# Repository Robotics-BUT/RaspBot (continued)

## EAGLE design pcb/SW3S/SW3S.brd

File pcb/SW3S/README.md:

Modul odpojovace 3-clankove baterie
===================================

Modul ma za ukol ovladat balancer po sbernici a dle vysledku ovladat povoleni 
zapinani a vypinani robota tak aby nedoslo k poskozeni baterie. Sekundarni funkci
je jednoduchy rezim nabijeni baterie za pomoci klasickeho 12V AC/DC adapteru
(trafo do zdi) a hlavne ovladani ukonceni nabijeni v okamziku dosazeni max
napeti na clanek.

Modul ve vypnutem stavu nesmi odebirat velky klidovy proud, pocita se s trvalym
pripojenim na baterii. Po stisku tlacitka (sepnuti spinace) si obvod zmeri kondici
baterie a usoudi zdali je mozno pripojit zbytek robota. Po pripojeni napajeni se
periodicky dotazuje balancovacich jednotek na stav a v pripade poklesu napeti k
3.2V/clanek automaticky odpoji zatez.

Po pripojeni externiho adapteru tuto udalost musi byt modul schopen zdetekovat a
zahajit nabijeni, pokud baterie jeste nema plny stav nabiti. Behem nabijeni opet
kontrolovat kondici baterie a pri jakemkoliv problemu (teplota nabijeciho T,
teplota jakehokoliv balancovaciho T, napeti na clanku) nabijeni odpojit. Pri
podbiti baterie pod 3V/clanek zakazat nabijeni.

Modul ma tez jistici funkci, proti zkratu na vystupu, zkratu na nabijeci
sbernici musi prehoret pojistka (prozatim rychla 2A) a nesmi se poskodit ani
elektronika ani baterie.

Pozadavky:
----------
Klidovy proud (OFF) = max 220 uA avg (vybije 2200mAh baterii za 1 rok)
Aktivni proud (ON) = max 10mA avg (dotazuje se na stav clanku)
Mereni teploty regulacniho tranzistoru, zakaz nabijeni nad danou mez)
Obousmerna komunikace s BAL3S
Nizka cena (vzhledem k cene baterie - tj pod 400kc/kus)
Velikost tak aby se modul dal prilepit na baterii a byl s ni trvale spojeny.

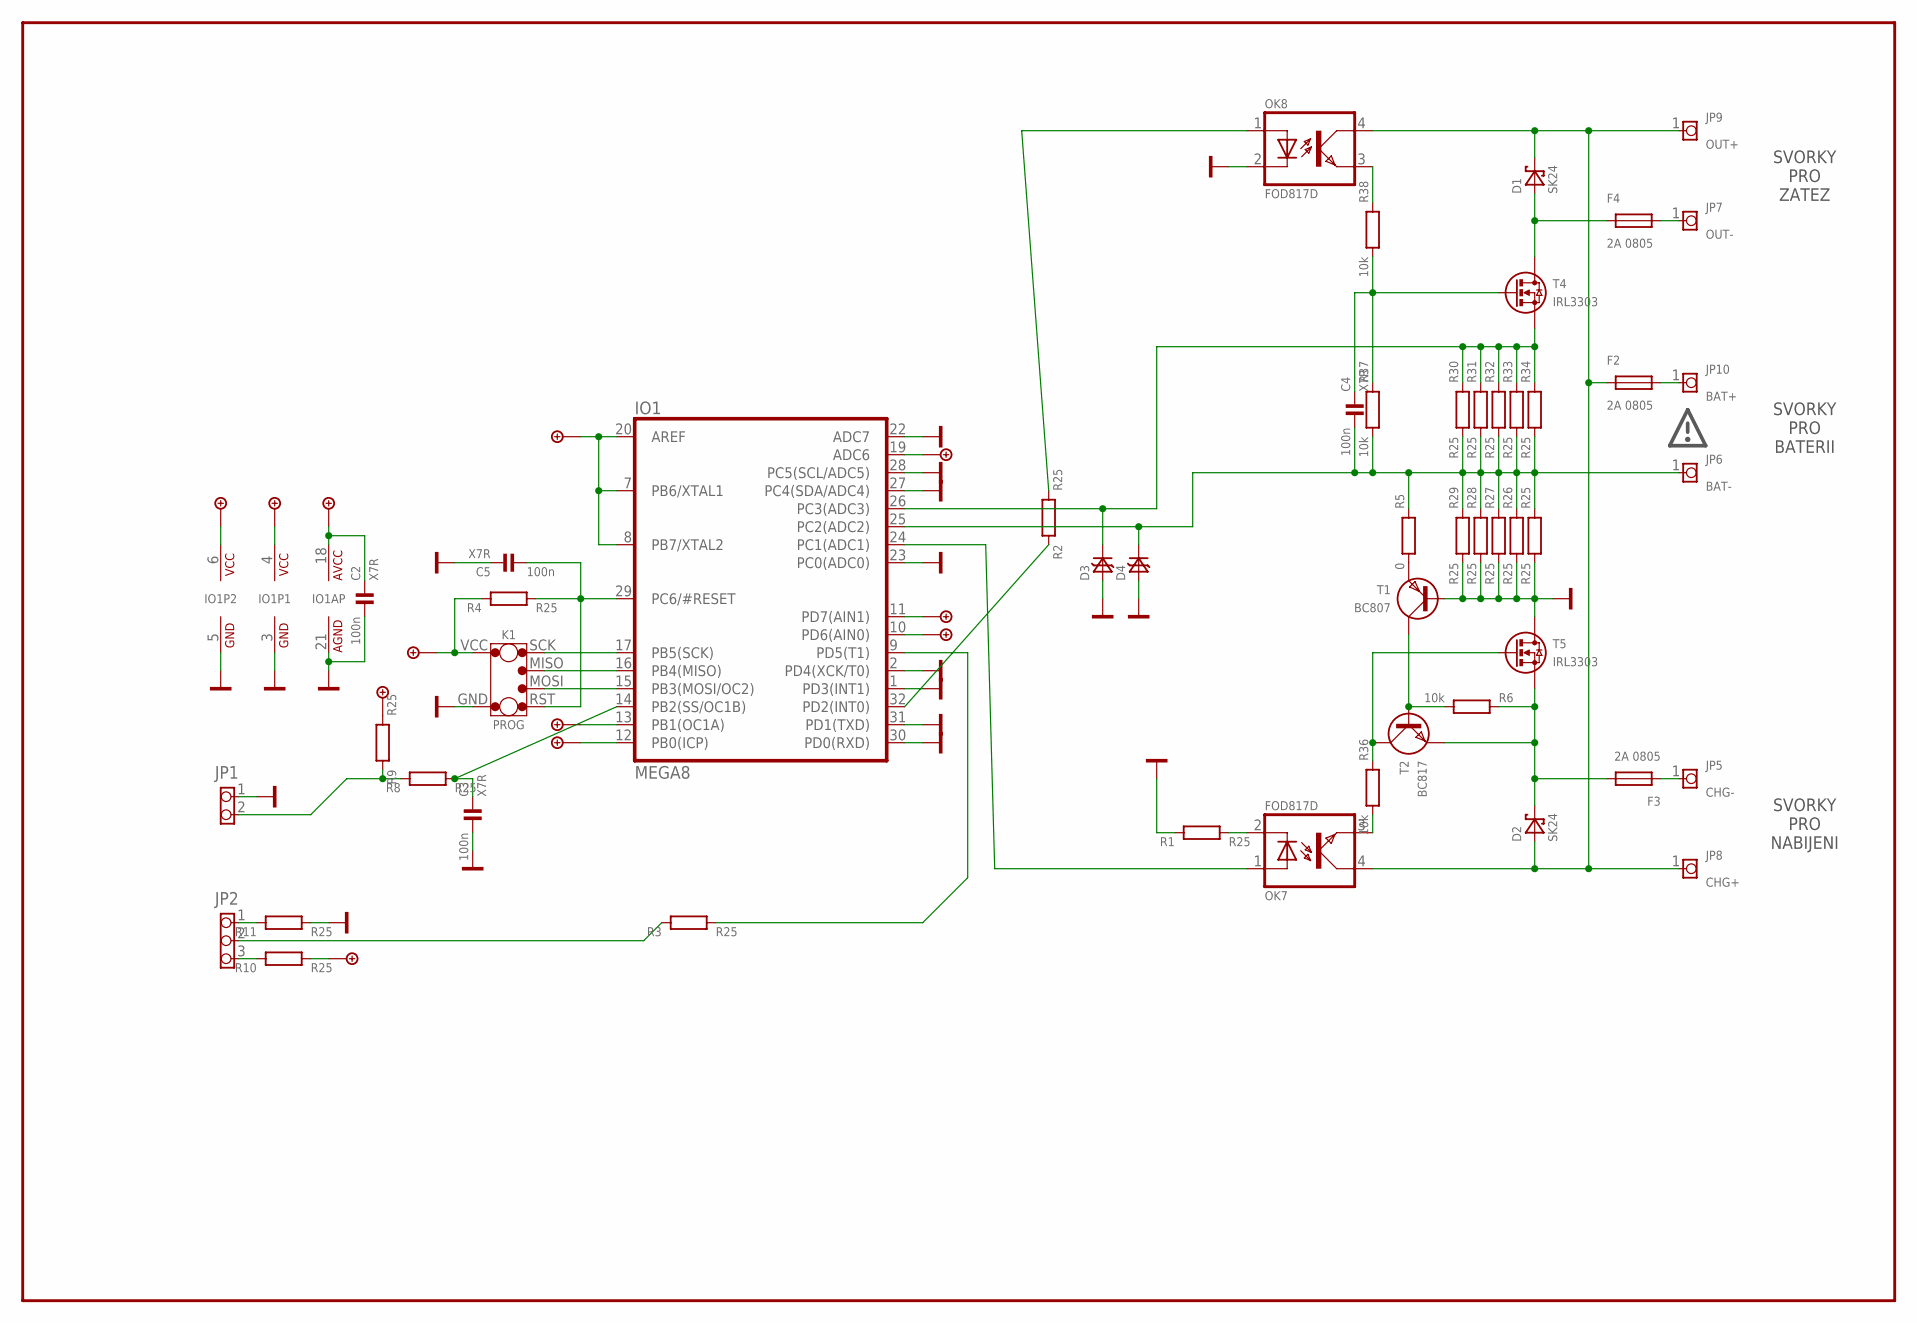
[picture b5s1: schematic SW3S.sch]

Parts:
C2, C3, C4, C5: 100n; 0805
D1, D2: SK24; D_SMB
D3, D4: D_TRANSIL_MLL34; D_MLL34
F2, F3, F4: 2A 0805; 0805
IO1: MEGA8; TQFP32
JP1: PINHD-1X2_254_EDGE; 1X02_254_EDGE
JP2: PINHD-1X3_254_EDGE; 1X03_254_EDGE
JP5: CHG-; 1X01_254_PAD
JP6: BAT-; 1X01_254_PAD
JP7: OUT-; 1X01_254_PAD
JP8: CHG+; 1X01_254_PAD
JP9: OUT+; 1X01_254_PAD
JP10: BAT+; 1X01_254_PAD
K1: PROG
OK7, OK8: FOD817D; SO04
R1, R2, R3, R4, R8, R9, R10, R11, R25, R26, R27, R28, R29, R30, R31, R32, R33, R34: R25; 0805
R5: 0; 0805
R6, R36, R37, R38: 10k; 0805
T1: BC807; SOT23
T2: BC817; SOT23
T4, T5: IRL3303; TO252

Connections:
+5V: C2.1, IO1.4 (VCC), IO1.6 (VCC), IO1.7 (PB6/XTAL1), IO1.8 (PB7/XTAL2), IO1.10 (PD6(AIN0)), IO1.11 (PD7(AIN1)), IO1.12 (PB0(ICP)), IO1.13 (PB1(OC1A)), IO1.18 (VCC), IO1.19 (ADC6), IO1.20 (AREF), K1.VCC, R4.2, R9.1, R10.1
BAT+: F2.2, JP10.1
BAT-: C4.2, D4.K, IO1.25 (PC2(ADC2)), JP6.1, R5.2, R25.2, R26.2, R27.2, R28.2, R29.2, R30.1, R31.1, R32.1, R33.1, R34.1, R37.1
CHG-: F3.1, JP5.1
GND: C2.2, C3.2, C5.1, D3.A, D4.A, IO1.1 (PD3(INT1)), IO1.2 (PD4(XCK/T0)), IO1.3 (GND), IO1.5 (GND), IO1.21 (GND), IO1.22 (ADC7), IO1.23 (PC0(ADC0)), IO1.27 (PC4(SDA/ADC4)), IO1.28 (PC5(SCL/ADC5)), IO1.30 (PD0(RXD)), IO1.31 (PD1(TXD)), JP1.1, K1.GND, OK8.2 (C), R1.2, R11.1, R25.1, R26.1, R27.1, R28.1, R29.1, T1.1 (B), T5.2 (D)
unnamed: IO1.17 (PB5(SCK)), K1.SCK
unnamed: IO1.16 (PB4(MISO)), K1.MISO
unnamed: IO1.15 (PB3(MOSI/OC2)), K1.MOSI
unnamed: C5.2, IO1.29 (PC6/#RESET), K1.RST, R4.1
unnamed: IO1.32 (PD2(INT0)), R2.2
unnamed: IO1.9 (PD5(T1)), R3.1
unnamed: R6.1, T1.2 (C), T2.1 (B)
unnamed: R36.2, T2.2 (C), T5.1 (G)
unnamed: OK7.3 (EMIT), R36.1
unnamed: IO1.24 (PC1(ADC1)), OK7.1 (A)
unnamed: D2.K, F3.2, R6.2, T2.3 (E), T5.3 (S)
unnamed: F4.2, JP7.1
unnamed: OK7.2 (C), R1.1
unnamed: C3.1, IO1.14 (PB2(SS/OC1B)), R8.1
unnamed: JP1.2, R8.2, R9.2
unnamed: JP2.2, R3.2
unnamed: JP2.3, R10.2
unnamed: JP2.1, R11.2
unnamed: R5.1, T1.3 (E)
unnamed: OK8.1 (A), R2.1
unnamed: D3.K, IO1.26 (PC3(ADC3)), R30.2, R31.2, R32.2, R33.2, R34.2, T4.3 (S)
unnamed: OK8.3 (EMIT), R38.2
unnamed: C4.1, R37.2, R38.1, T4.1 (G)
OUT+: D1.K, D2.A, F2.1, JP8.1, JP9.1, OK7.4 (COL), OK8.4 (COL)
OUT-: D1.A, F4.1, T4.2 (D)

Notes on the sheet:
SVORKY PRO ZATEZ
SVORKY PRO BATERII
SVORKY PRO NABIJENI

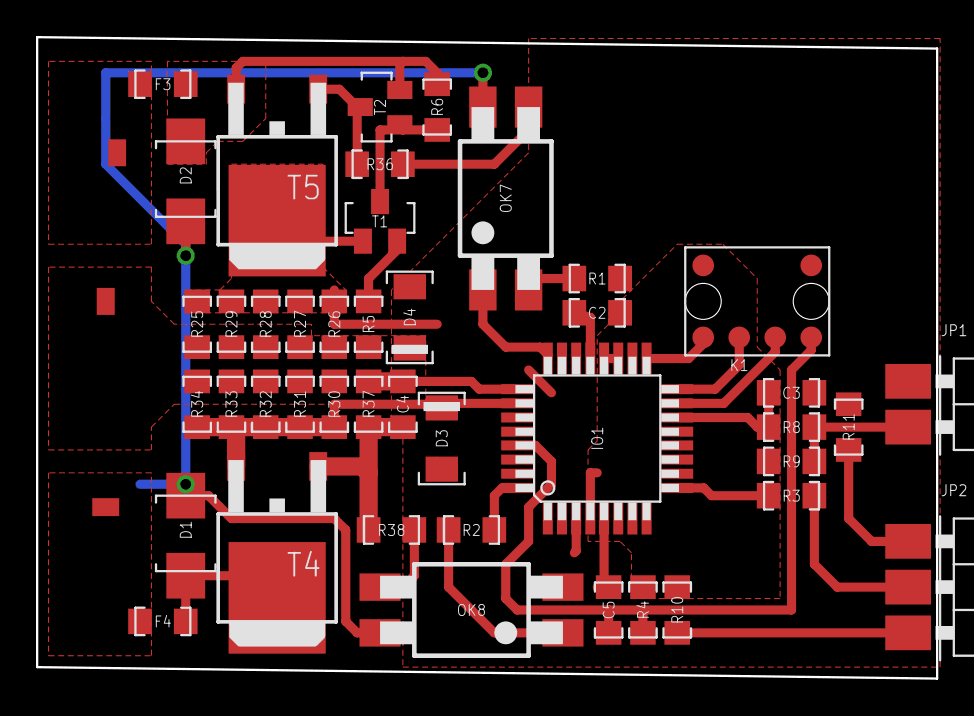
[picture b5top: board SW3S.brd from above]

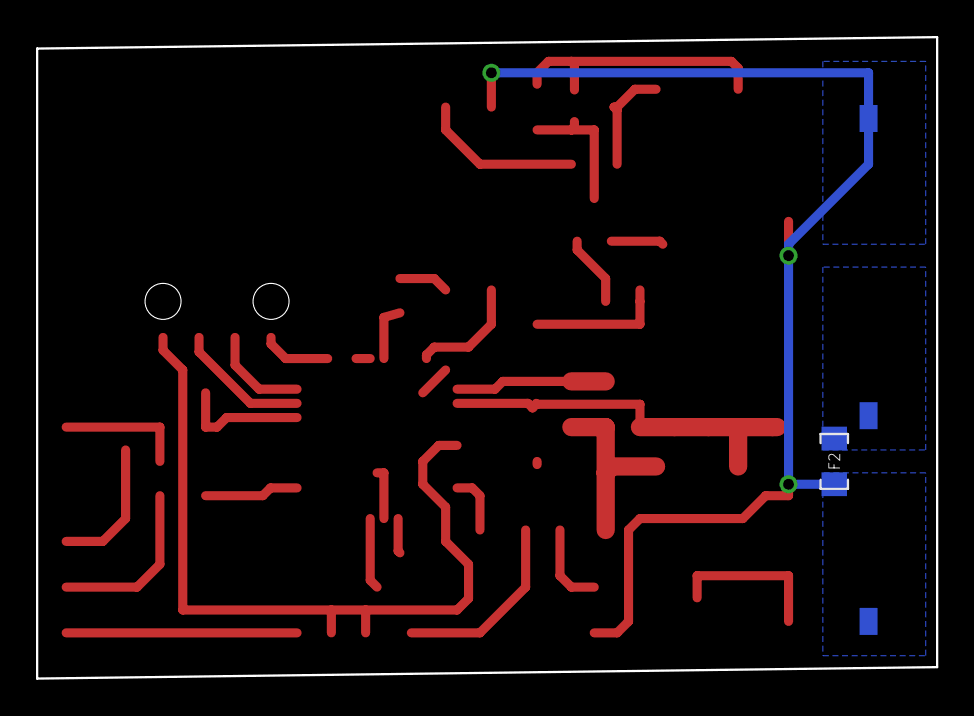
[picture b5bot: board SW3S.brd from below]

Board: 2 copper layers, 50.0 x 35.6 mm, 50 parts (4 on the bottom side), 30 nets.

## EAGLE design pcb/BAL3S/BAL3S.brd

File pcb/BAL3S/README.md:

Modul balanceru 3-clankove baterie
==================================

Modul ma za ukol merit napeti na jednotlivych clancich baterie a nasledne
stavove informace posilat ven pomoci sbernice. Pokud neni pripojen master
na sbernici, je nutne odpojit balancovani a mit nizkou spotrebu vzhledem ke
kapacite baterie.

Pozadavky:
----------
Klidovy proud = max 220 uA avg (vybije 2200mAh baterii za 1 rok)
Balancovaci proud = cca 100 mA DC / clanek (0.5W/clanek je treba uchladit)
Aktivni proud = max 2mA avg (master se dotazuje na stav clanku)
Mereni napeti kazdeho clanku 4.200V s rozlisenim +- 5mV (10 bit ADC}
Mereni teploty topneho tranzistoru, zakaz balancovani nad danou mez)
Obousmerna komunikace s vyvazovacim procesorem kazdeho clanku
Moznost kalibrace mereneho napeti pres sbernici (vicebod ?)
Nizka cena (vzhledem k cene baterie - tj pod 400kc/kus)
Velikost tak aby se modul dal prilepit na baterii a byl s ni trvale spojeny.

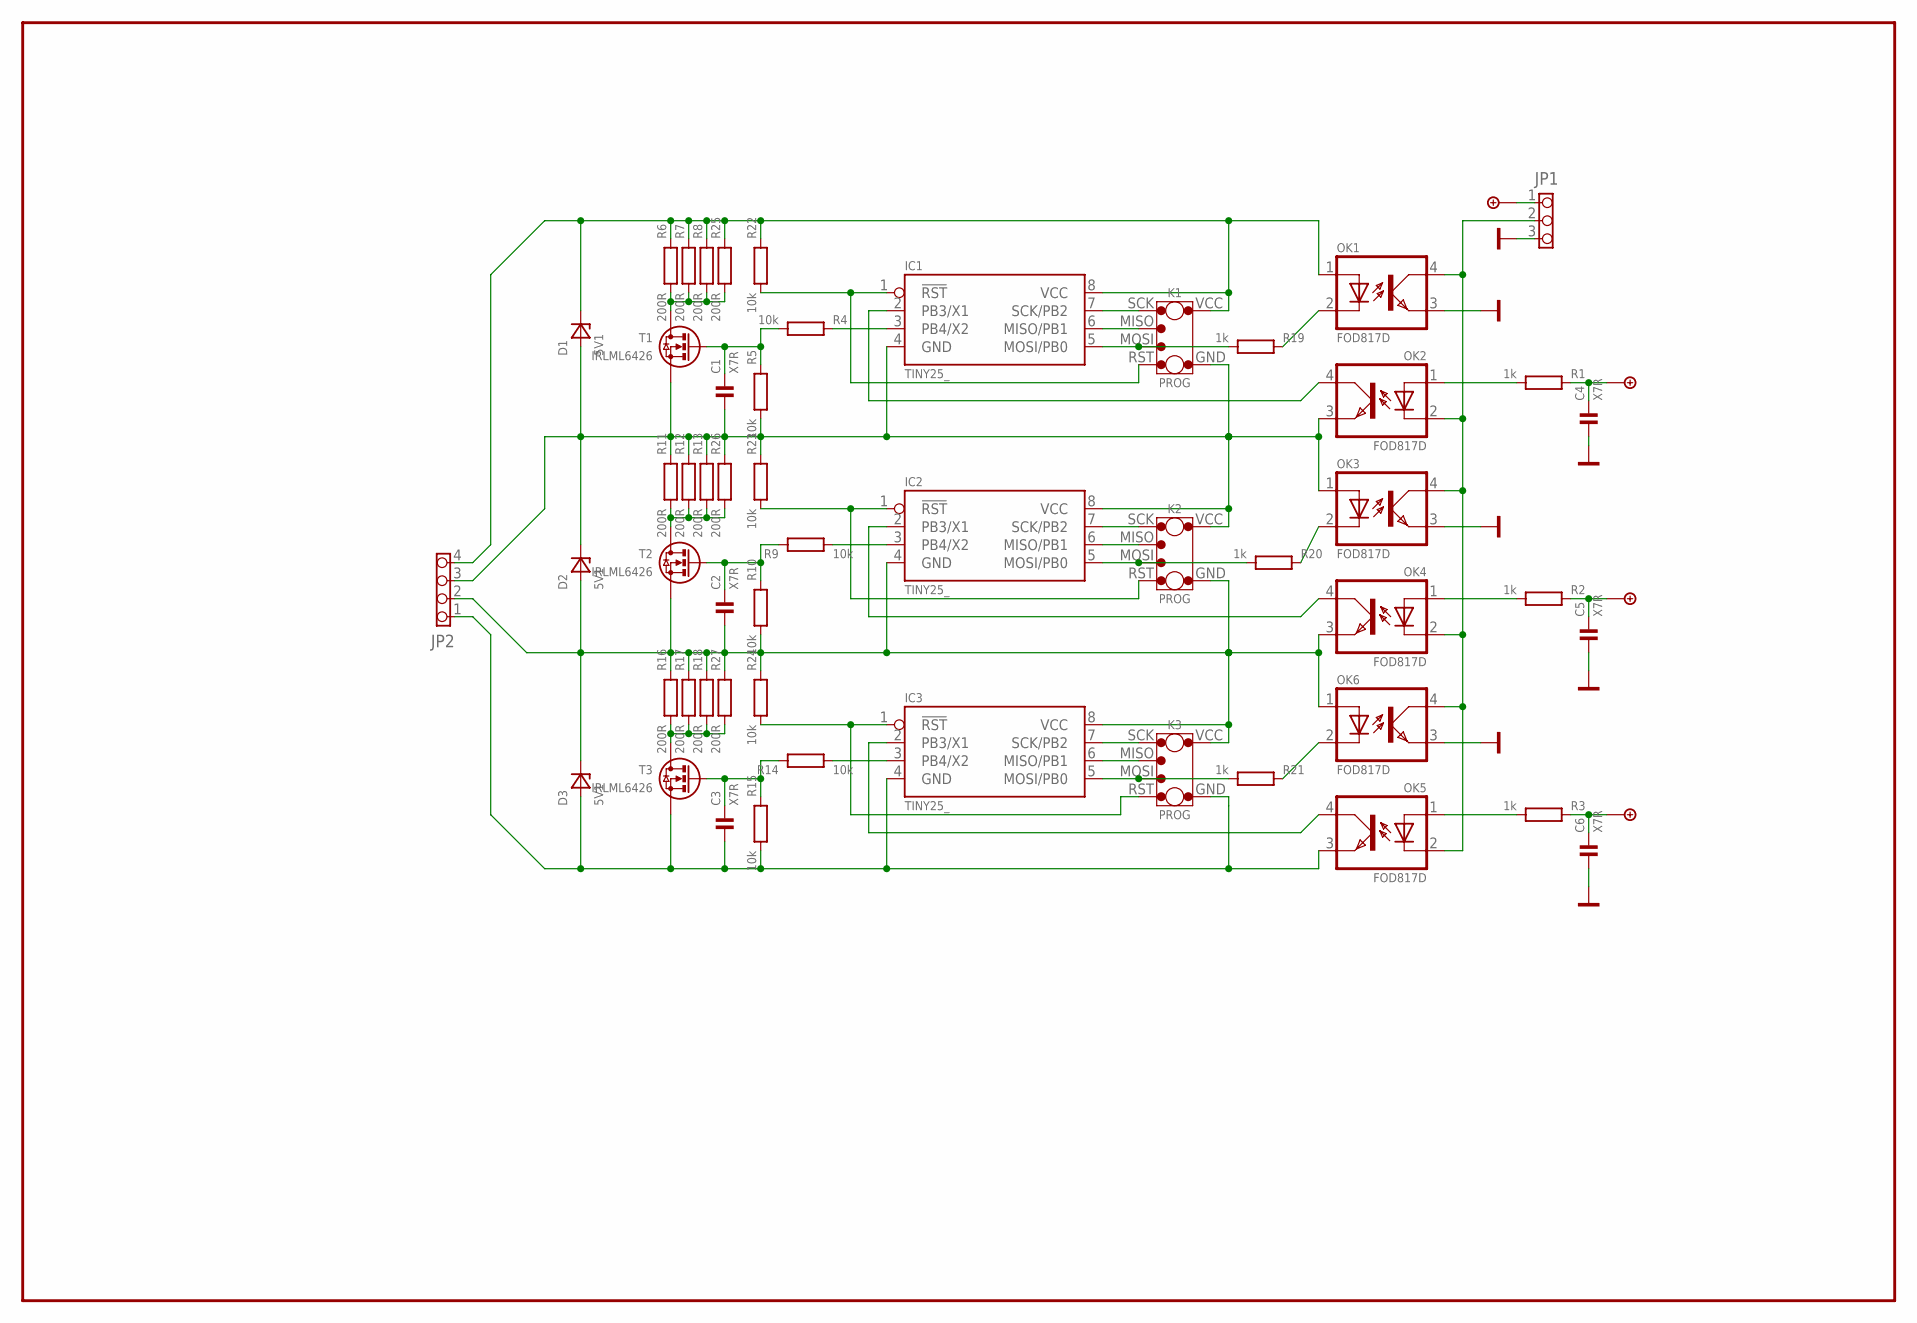
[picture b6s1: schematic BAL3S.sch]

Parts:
C1, C2, C3, C4, C5, C6: C0805; 0805
D1, D2, D3: 5V1; D_MLL41
IC1, IC2, IC3: TINY25_; SO08
JP1: PINHD-1X3_254_EDGE; 1X03_254_EDGE
JP2: PINHD-1X4_254_EDGE; 1X04_254_EDGE
K1, K2, K3: PROG
OK1, OK2, OK3, OK4, OK5, OK6: FOD817D; SO04
R1, R2, R3, R19, R20, R21: 1k; 0805
R4, R5, R9, R10, R14, R15, R22, R23, R24: 10k; 0805
R6, R7, R8, R11, R12, R13, R16, R17, R18, R25, R26, R27: 200R; 0805
T1, T2, T3: IRLML6426; SOT23

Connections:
+5V: C4.1, C5.1, C6.1, JP1.1, R1.2, R2.2, R3.2
GND: C4.2, C5.2, C6.2, JP1.3, OK1.3 (EMIT), OK3.3 (EMIT), OK6.3 (EMIT)
unnamed: C1.2, D1.A, D2.K, IC1.4 (GND), IC2.8 (VCC), JP2.3, K1.GND, K2.VCC, OK2.3 (EMIT), OK3.1 (A), R5.1, R11.2, R12.2, R13.2, R23.2, R26.2, T1.3 (S)
unnamed: C2.2, D2.A, D3.K, IC2.4 (GND), IC3.8 (VCC), JP2.2, K2.GND, K3.VCC, OK4.3 (EMIT), OK6.1 (A), R10.1, R16.2, R17.2, R18.2, R24.2, R27.2, T2.3 (S)
unnamed: C3.2, D3.A, IC3.4 (GND), JP2.1, K3.GND, OK5.3 (EMIT), R15.1, T3.3 (S)
unnamed: IC1.3 (PB4/X2), R4.2
unnamed: JP1.2, OK1.4 (COL), OK2.2 (C), OK3.4 (COL), OK4.2 (C), OK5.2 (C), OK6.4 (COL)
unnamed: OK2.1 (A), R1.1
unnamed: OK4.1 (A), R2.1
unnamed: OK5.1 (A), R3.1
unnamed: C1.1, R4.1, R5.2, T1.1 (G)
unnamed: IC1.2 (PB3/X1), OK2.4 (COL)
unnamed: IC1.7 (SCK/PB2), K1.SCK
unnamed: R6.1, R7.1, R8.1, R25.1, T1.2 (D)
unnamed: C2.1, R9.2, R10.2, T2.1 (G)
unnamed: D1.K, IC1.8 (VCC), JP2.4, K1.VCC, OK1.1 (A), R6.2, R7.2, R8.2, R22.2, R25.2
unnamed: IC2.3 (PB4/X2), R9.1
unnamed: IC2.2 (PB3/X1), OK4.4 (COL)
unnamed: R11.1, R12.1, R13.1, R26.1, T2.2 (D)
unnamed: IC1.6 (MISO/PB1), K1.MISO
unnamed: IC3.3 (PB4/X2), R14.1
unnamed: C3.1, R14.2, R15.2, T3.1 (G)
unnamed: R16.1, R17.1, R18.1, R27.1, T3.2 (D)
unnamed: IC1.5 (MOSI/PB0), K1.MOSI, R19.1
unnamed: IC1.1 (!RST), K1.RST, R22.1
unnamed: IC2.7 (SCK/PB2), K2.SCK
unnamed: IC2.6 (MISO/PB1), K2.MISO
unnamed: IC2.5 (MOSI/PB0), K2.MOSI, R20.1
unnamed: IC3.7 (SCK/PB2), K3.SCK
unnamed: IC2.1 (!RST), K2.RST, R23.1
unnamed: IC3.6 (MISO/PB1), K3.MISO
unnamed: IC3.5 (MOSI/PB0), K3.MOSI, R21.1
unnamed: IC3.1 (!RST), K3.RST, R24.1
unnamed: IC3.2 (PB3/X1), OK5.4 (COL)
unnamed: OK1.2 (C), R19.2
unnamed: OK3.2 (C), R20.2
unnamed: OK6.2 (C), R21.2

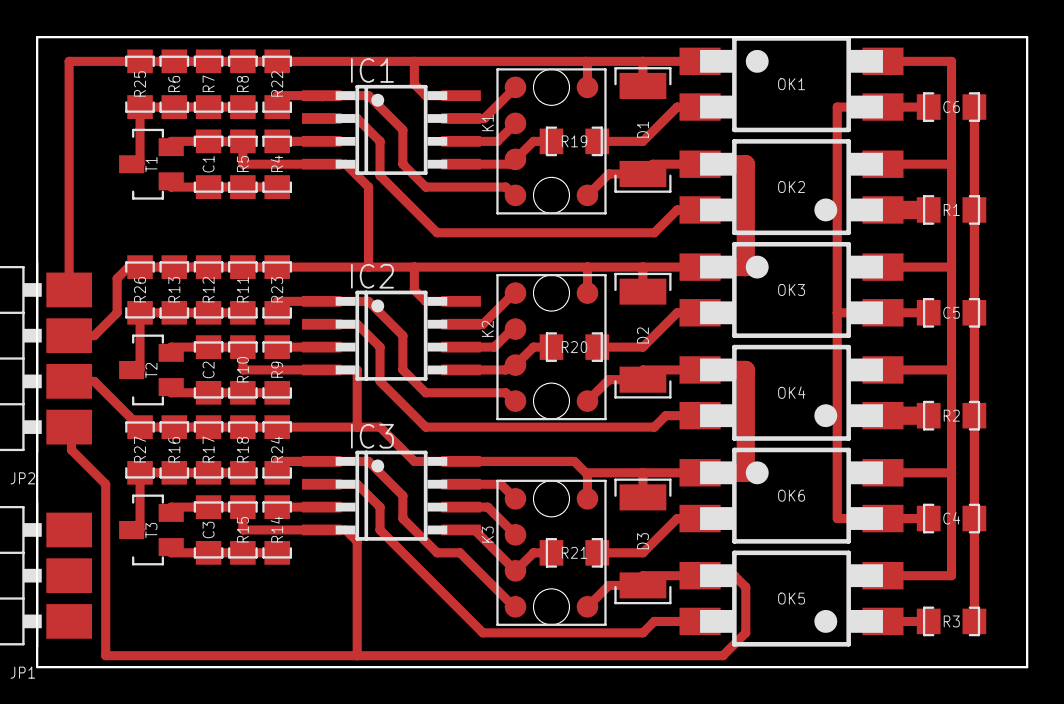
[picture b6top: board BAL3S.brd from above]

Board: 2 copper layers, 55.0 x 35.0 mm, 53 parts (0 on the bottom side), 37 nets.

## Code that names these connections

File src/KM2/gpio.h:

#ifndef GPIO_H__
#define GPIO_H__

#include <stdbool.h>
#include <avr/io.h>

/*
 * KM2/gpio.h:
 *	gpio low level module
 *
 * Copyright (c) 2016 Frantisek Burian <BuFran@seznam.cz>
 ***********************************************************************
 * This file is part of KAMBot
 *
 *    KAMBot is free software: you can redistribute it and/or modify
 *    it under the terms of the GNU Lesser General Public License as published by
 *    the Free Software Foundation, either version 3 of the License, or
 *    (at your option) any later version.
 *
 *    KAMBot is distributed in the hope that it will be useful,
 *    but WITHOUT ANY WARRANTY; without even the implied warranty of
 *    MERCHANTABILITY or FITNESS FOR A PARTICULAR PURPOSE.  See the
 *    GNU Lesser General Public License for more details.
 *
 *    You should have received a copy of the GNU Lesser General Public License
 *    along with KAMBot.  If not, see <http://www.gnu.org/licenses/>.
 ***********************************************************************
 */

#define _PA		(0 << 4)
#define _PA0	(_PA + 0)
#define _PA1	(_PA + 1)
#define _PA2	(_PA + 2)
#define _PA3	(_PA + 3)
#define _PA4	(_PA + 4)
#define _PA5	(_PA + 5)
#define _PA6	(_PA + 6)
#define _PA7	(_PA + 7)

#define _PB		(1 << 4)
#define _PB0	(_PB + 0)
#define _PB1	(_PB + 1)
#define _PB2	(_PB + 2)
#define _PB3	(_PB + 3)
#define _PB4	(_PB + 4)
#define _PB5	(_PB + 5)
#define _PB6	(_PB + 6)
#define _PB7	(_PB + 7)

#define _PC		(2 << 4)
#define _PC0	(_PC + 0)
#define _PC1	(_PC + 1)
#define _PC2	(_PC + 2)
#define _PC3	(_PC + 3)
#define _PC4	(_PC + 4)
#define _PC5	(_PC + 5)
#define _PC6	(_PC + 6)
#define _PC7	(_PC + 7)

#define _PD		(3 << 4)
#define _PD0	(_PD + 0)
#define _PD1	(_PD + 1)
#define _PD2	(_PD + 2)
#define _PD3	(_PD + 3)
#define _PD4	(_PD + 4)
#define _PD5	(_PD + 5)
#define _PD6	(_PD + 6)
#define _PD7	(_PD + 7)

#define _PE		(4 << 4)
#define _PE0	(_PE + 0)
#define _PE1	(_PE + 1)
#define _PE2	(_PE + 2)
#define _PE3	(_PE + 3)
#define _PE4	(_PE + 4)
#define _PE5	(_PE + 5)
#define _PE6	(_PE + 6)
#define _PE7	(_PE + 7)

#define _PF		(5 << 4)
#define _PF0	(_PF + 0)
#define _PF1	(_PF + 1)
#define _PF2	(_PF + 2)
#define _PF3	(_PF + 3)
#define _PF4	(_PF + 4)
#define _PF5	(_PF + 5)
#define _PF6	(_PF + 6)
#define _PF7	(_PF + 7)

#define __PORT(pin)		(pin & 0xF0)
#define __PIN(pin)		(pin & 0x0F)
#define __PINBIT(pin)	(1 << (pin & 0x0F))

inline void gpio_out(const char pin)
{
	switch (__PORT(pin)) {
//		case _PA: DDRA &= ~__PINBIT(pin); break;
		case _PB: DDRB &= ~__PINBIT(pin); break;
		case _PC: DDRC &= ~__PINBIT(pin); break;
		case _PD: DDRD &= ~__PINBIT(pin); break;
	}
}

inline void gpio_in(const char pin)
{
	switch (__PORT(pin)) {
//		case _PA: DDRA |= __PINBIT(pin); break;
		case _PB: DDRB |= __PINBIT(pin); break;
		case _PC: DDRC |= __PINBIT(pin); break;
		case _PD: DDRD |= __PINBIT(pin); break;
	}
}

inline void gpio_high(const char pin)
{
	switch (__PORT(pin)) {
//		case _PA: PORTA |= __PINBIT(pin); break;
		case _PB: PORTB |= __PINBIT(pin); break;
		case _PC: PORTC |= __PINBIT(pin); break;
		case _PD: PORTD |= __PINBIT(pin); break;
	}
}

inline void gpio_low(const char pin)
{
	switch (__PORT(pin)) {
	//	case _PA: PORTA &= ~__PINBIT(pin); break;
		case _PB: PORTB &= ~__PINBIT(pin); break;
		case _PC: PORTC &= ~__PINBIT(pin); break;
		case _PD: PORTD &= ~__PINBIT(pin); break;
	}
}

inline void gpio_toggle(const char pin)
{
	switch (__PORT(pin)) {
	//	case _PA: PORTA ^= __PINBIT(pin); break;
		case _PB: PORTB ^= __PINBIT(pin); break;
		case _PC: PORTC ^= __PINBIT(pin); break;
		case _PD: PORTD ^= __PINBIT(pin); break;
	}
}

inline void gpio_set(const char pin, const char value)
{
	switch (__PORT(pin)) {
#ifdef PORTA
		case _PA:
			if (value) PORTA |= __PINBIT(pin);
			else PORTA &= ~__PINBIT(pin);
			break;
#endif
#ifdef PORTB
		case _PB:
			if (value) PORTB |= __PINBIT(pin);
			else PORTB &= ~__PINBIT(pin);
			break;
#endif
#ifdef PORTC
		case _PC:
			if (value) PORTC |= __PINBIT(pin);
			else PORTC &= ~__PINBIT(pin);
			break;
#endif
#ifdef PORTD
		case _PD:
			if (value) PORTD |= __PINBIT(pin);
			else PORTD &= ~__PINBIT(pin);
			break;
#endif
	}
}

inline bool gpio_get(const char pin)
{
	switch (__PORT(pin)) {
	//	case _PA: return (PINA & __PINBIT(pin)) != 0;
		case _PB: return (PINB & __PINBIT(pin)) != 0;
		case _PC: return (PINC & __PINBIT(pin)) != 0;
		case _PD: return (PIND & __PINBIT(pin)) != 0;
	}
}


#endif //GPIO_H

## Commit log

2015-09-23 Added primary base tests of the platform
2015-09-23 Added readme
2015-09-23 Changed build system
2015-09-27 Added header library with pin definitions
2015-10-01 Pridan testovaci firmware pro cteni MCP3424 !! nutne opravy v knihovne wiringPi
2015-10-01 Added bigstepping - now very fast rotation
2015-10-02 Dual motor control
2015-10-02 Modified and fully working with joystick and dual motors
2015-10-02 Added UDP interface to Raspbot
2016-03-08 Pridana prvni verze plosnych spoju pro APU * jednotka BAL3S pro 3clankovy balancer * SW3S pro autimaticky odpojovac a nabijec
    momentalne je verze kdy lze nabijeci proud ridit (bude odstraneno)
2016-03-08 Pridany temporary soubory Eagle jako ignorovane
2016-03-08 Regulace maximalniho nabijeciho proudu neni potreba
    V prvni fazi se nabiji baterie konstantnim proudem a v pripade dosazeni U 4.15V/clanek (rezerva 50mV) se nabijeni uplne odpoji.
    V pripade kdy balancer nebude stihat vyvazit baterii se tez nabijeni odpoji do okamziku vyvazeni vsech clanku baterie pod mez danou fw.
    V pripade podvybiti baterie pod 3V elektronika nepovoli nabijeni (baterii je nutno nabit externi "inteligentni" nabijeckou.
    Pozor:
    Je potreba nabijet ze zdroje 12-14V kvuli ubytku napeti / ztratovem vykonu na regulacnim tranzistoru.
    Ve firmware musi byt odpojeni nabijeni v pripade prehrati CPU nad stanovenou, docela nizkou mez !!! (CPU je blizko regulacniho T)
2016-03-08 Prvni verze ovladace dvou krokovych motoru KM2
    Tato verze vychazi z hw 0.2, je potreba velky redesign pro snizeni montazni vysky. Vyuziti 2v DPS a drivery se budou pajet rovnou, bez patic.
    Je potreba tez specifikovat velikost DPS (probrat s navrharem mechanicke konstrukce)
2016-03-08 Vytvoreny slozky pro firmware modulu BAL3S, SW3S a KM2
2016-03-08 Pridany popisne soubory popisujici funkci jednotilvych modulu
2016-03-08 Zmena nazvu robota
2016-03-08 Pridany dalsi slozky stromove struktury projektu
2016-03-09 blikani s vypisem
2016-03-10 Pridana dokumentace modulu RPIV00 a error list.
2016-03-10 STL soubory pro uplne prvni verzi KAMBotu
2016-03-10 Pridana sestava pro prvni verzi plastovych dilu KAMbotu
2016-03-10 Pridana sestava mechanicke konstrukce KAMBot v 0.2
2016-03-10 KM2 - vycisteni schematu, finalizace pred vyrobou
2016-03-11 Finalizace modulu KM2, vyroba
2016-03-11 Added PROG holder first version
2016-03-11 Redesign programovaciho pripravku
2016-03-11 Created first version of firmware of KM2
2016-04-28 komentare
2016-04-28 nothing
2016-04-28 modified
2016-04-28 first commit from terminal
2016-04-28 robot korektne jezdi vlevo a vpravo (klavesnice)
2016-04-28 posledni verze
2016-09-29 Pridan tool pro vysilani broadcastu protokolu MNDP (Mikrotik Network Doscovery Protocol) Jadro aplikace napsal student Ladislav Tylich Tato commitovana verze je vycistena a upravena Frantiskem Burian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
2016-10-11 Designed new GPIO module
2016-10-11 Added header info
2016-10-11 Pridany funkce pro plnou manipulaci s GPIO
2016-10-11 km2 final version of firmware
2016-10-24 Add GUI for remote control
2016-10-24 Pridan GUI Remote Control binary
2016-11-01 pridany sdilene knihovny pro I2C a ADC
2016-11-01 Pridany funce pro operace s poli
2016-11-02 I2C: zprehledneno API knihovny
2016-11-02 I2C: Pridana dokumentace funkci, pridano cteni pole hodnot
2016-11-02 Pridana knhovna pro komunikaci s menicem motoru KM2
2016-11-03 Pridana dokumentace modulu ADC, vcetne vygenerovaneho 3D modelu pro SketchUp
2016-11-03 3D model ADC presunut do podadresare RevB
2016-11-03 KM2: Finalizovany plosny spoj KM2, 3D model, vyrobni data pool servisu APAMA, partlist, osazovaky, Prvni verze firmware
2016-11-03 KM2: Přidán první errata
2016-11-03 KM2: přidán soubor s projektem EAGLE
2016-11-03 ignorovat soubory generovane z C# projektu z Visual Studia
2016-11-03 Pridana dokumentace modulu ADC RevB
2016-11-04 Aktualizovany partlisty u obou modulu KM2 i ADC. Odkazy a ceny jsou uvnitr schematu.
2016-11-04 Pridan solution pro AtmelStudio
2016-11-04 KM2: Odstranen stary Makefile, upraven gitignore aby reflektoval build AtmelStudia
2016-11-04 KM2: predelano na kompatibilitu s util/twi.h
2016-11-04 KM2: novy firmware mnoho funkci navic:
    * funkcni obousmerna komunikace po I2C,
    * diferencialni odometrie,
    * parametrizace regulatoru pres i2c registry,
    * nastaveni hodnot pri bootu pres eeprom,
    * automaticke zastaveni bez prijimanych dat v casovem okne
    * automaticke odpojeni proudu do motoru pri delsi dobe necinnosti robotu (ochrana proti tepelnemu namahani)
2016-11-07 Pridan driver chipu BQ769x0
2017-01-30 Pridana moznost preneseni 0 bytu dat pri zapisu
2017-06-27 Upraven README - dokumentace protokolu
2017-06-27 Přidána základní rozšiřujcí deska
    Vytvořeno v rámci práce "Rozšiřující deska pro RaspberryPi" studentem Tadeášem Diváckým v rámci BP
    Bakalářskou práci lze nalézt i s přílohami na www.vutbr.cz
2017-06-27 Přidány opravy chyb, které se vyskytly během oživování
2017-06-27 Přidány programy do RaspberryPi odevzdané v BP, související s MAINBOARD
2017-07-20 Velke upravy pred odeslanim do seriove vyroby
2017-07-26 New version of board, shipped to SeedStudio (2x KM2-B, 1x Mainboard -A)
2017-07-27 KM2 a MAINBOARD - posledni upravy pred Release
2017-07-27 Plosne spoje pro vyuku ve finalni verzi presunuty do separatnich submodulu ze serveru VUT
2017-07-27 Aktualizovany submoduly
2017-09-15 HTTPS mode for submodules
    Submoduly jsou nyni volne dostupne pomoci HTTPS protokolu bez hesla
2017-10-18 Uprava firmware pro KM2-B
